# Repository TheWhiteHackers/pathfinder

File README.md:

# Pathfinder
For week four of Half Life I created a board that can be used for multiple things.

## Fidget...
The board can be used as a fidget with 4 buttons when it is not plugged into the computer

## ...and Play Games
I programed the board where the 4 buttons can be used to play arrow/WASD games!

## Additionally, Try a Simon Says & Wack-A-Mole Game
I also made a simon says and wack-a-mole game that people can play if they want to stop using the device to play games!

## Programs Used
For this project I used KiCAD for making the board and Arduino IDE to code the board.

## Future!
Since I can change the code in the future, this can also be used to play different games. For example, some used this to play a morse code or guess-the-seconds type games!

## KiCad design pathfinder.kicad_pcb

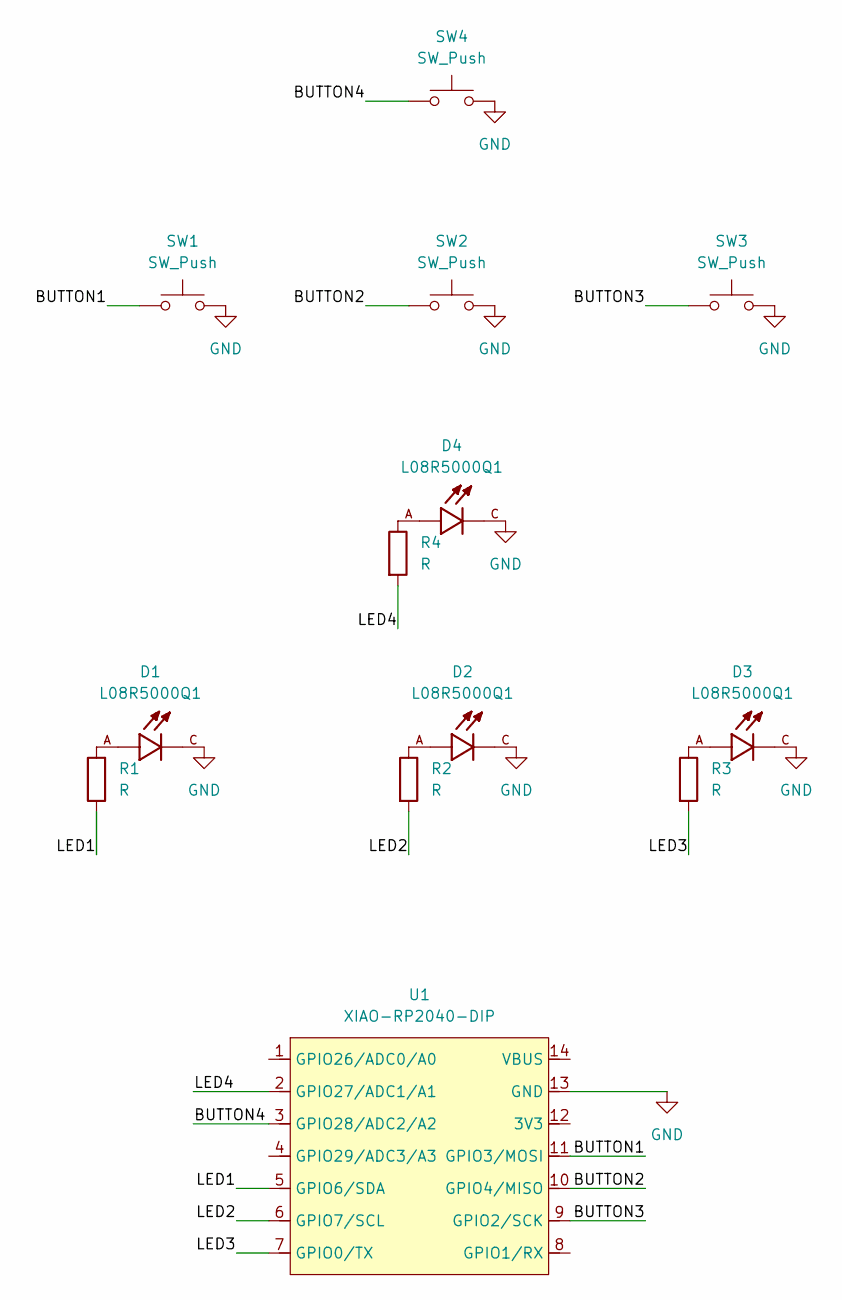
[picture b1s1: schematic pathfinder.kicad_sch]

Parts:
D1, D2, D3, D4: L08R5000Q1; LEDRD254W57D500H1070; PARTREV NA
R1, R2, R3, R4: R; R_Axial_DIN0204_L3.6mm_D1.6mm_P5.08mm_Horizontal
SW1, SW2, SW3, SW4: SW_Push; SW_Cherry_MX_1.00u_PCB
U1: XIAO-RP2040-DIP

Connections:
/BUTTON1: SW1.1, U1.11 (GPIO3/MOSI)
/BUTTON2: SW2.1, U1.10 (GPIO4/MISO)
/BUTTON3: SW3.1, U1.9 (GPIO2/SCK)
/BUTTON4: SW4.1, U1.3 (GPIO28/ADC2/A2)
/LED1: R1.1, U1.5 (GPIO6/SDA)
/LED2: R2.2, U1.6 (GPIO7/SCL)
/LED3: R3.2, U1.7 (GPIO0/TX)
/LED4: R4.2, U1.2 (GPIO27/ADC1/A1)
GND: D1.C, D2.C, D3.C, D4.C, SW1.2, SW2.2, SW3.2, SW4.2, U1.13 (GND)
unnamed: D1.A, R1.2
unnamed: D2.A, R2.1
unnamed: D3.A, R3.1
unnamed: D4.A, R4.1

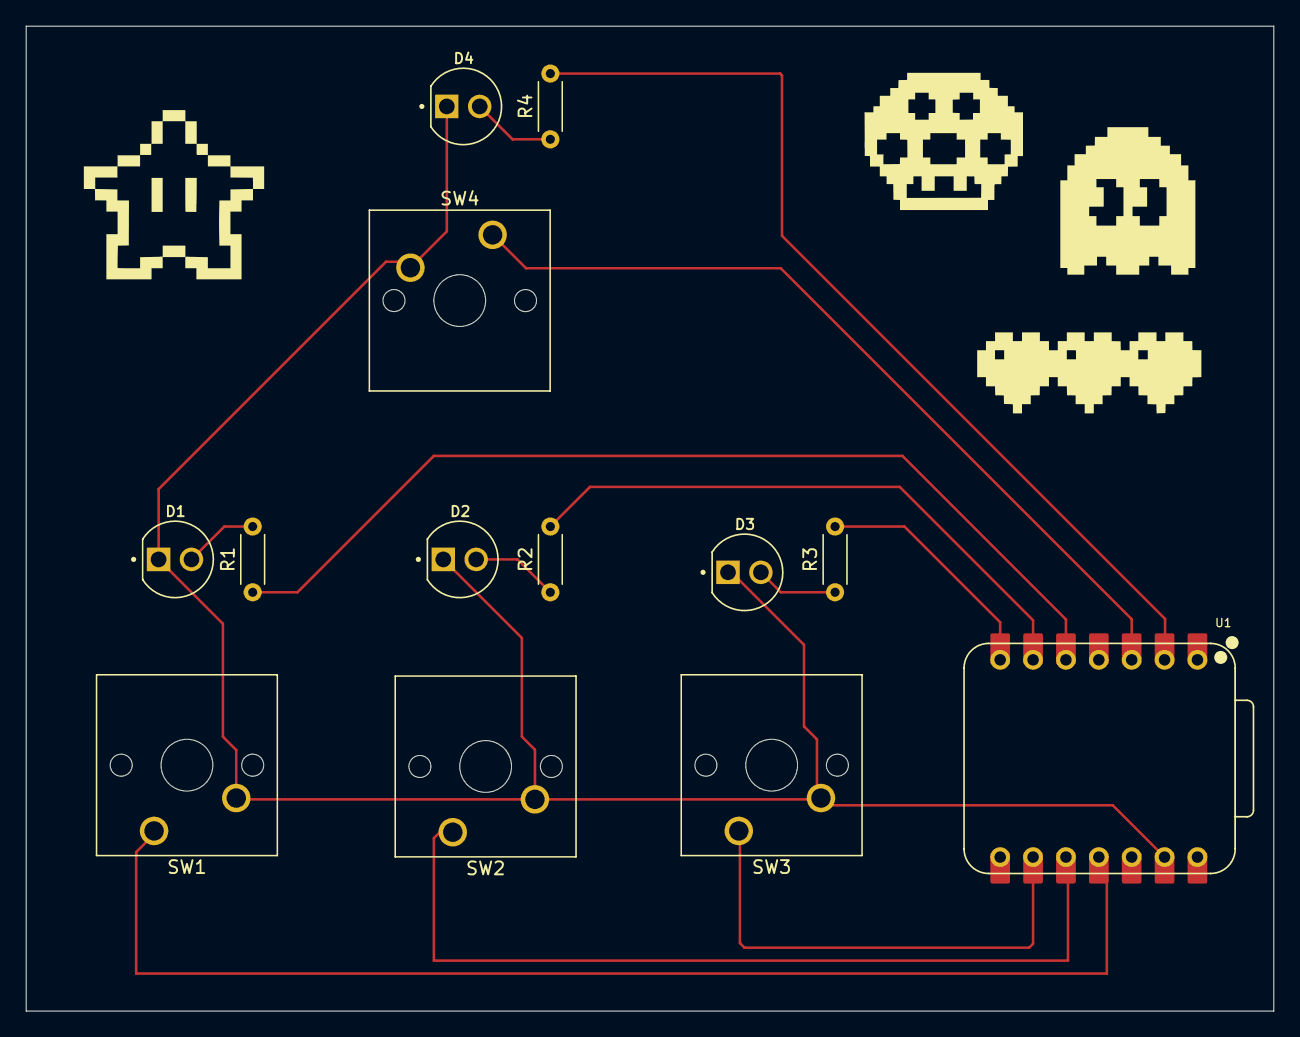
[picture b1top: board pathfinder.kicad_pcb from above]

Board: 2 copper layers, 96.4 x 76.1 mm, 13 parts (0 on the bottom side), 13 nets.

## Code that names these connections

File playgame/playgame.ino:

#include <Keyboard.h>

int BUT1 = D10; // left + a
int BUT2 = D9; // down + s
int BUT3 = D8; // right + d
int BUT4 = D2; // up + w

int LED1 = D4;
int LED2 = D5;
int LED3 = D6;
int LED4 = D1;


void setup() {
  // put your setup code here, to run once:
  pinMode(BUT1, INPUT_PULLUP);
  pinMode(BUT2, INPUT_PULLUP);
  pinMode(BUT3, INPUT_PULLUP);
  pinMode(BUT4, INPUT_PULLUP);


  pinMode(LED1, OUTPUT);
  pinMode(LED2, OUTPUT);
  pinMode(LED3, OUTPUT);
  pinMode(LED4, OUTPUT);

  Keyboard.begin();
  delay(1000);

}

void loop() {
  // put your main code here, to run repeatedly:
  // lights up button 1 if pressed
  if (digitalRead(BUT1) == HIGH){
    digitalWrite(LED1, HIGH);
  } else {
    digitalWrite(LED1, LOW);
  }
  // lights up button 2 if pressed
  if (digitalRead(BUT2) == HIGH){
    digitalWrite(LED2, HIGH);
  } else {
    digitalWrite(LED2, LOW);
  }
  // lights up button 3 if pressed
  if (digitalRead(BUT3) == HIGH){
    digitalWrite(LED3, HIGH);
  } else {
    digitalWrite(LED3, LOW);
  }
  // lights up button 4 if pressed
  if (digitalRead(BUT4) == HIGH){
    digitalWrite(LED4, HIGH);
  } else {
    digitalWrite(LED4, LOW);
  }

  handleButton(BUT1, "a", KEY_LEFT_ARROW);
  handleButton(BUT2, "s", KEY_DOWN_ARROW);
  handleButton(BUT3, "d", KEY_RIGHT_ARROW);
  handleButton(BUT4, "w", KEY_UP_ARROW);

}

void handleButton(int pin, char asciiKey, uint8_t theKey) {
  if (digitalRead(pin) == LOW){
    Keyboard.press(asciiKey);
    Keyboard.press(theKey);
  } else {
    Keyboard.release(asciiKey);
    Keyboard.release(theKey);
  }
}
